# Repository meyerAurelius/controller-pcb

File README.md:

# controller-pcb
Controller PCB for the Digital Dash on the UCalgary BAJA Student design team

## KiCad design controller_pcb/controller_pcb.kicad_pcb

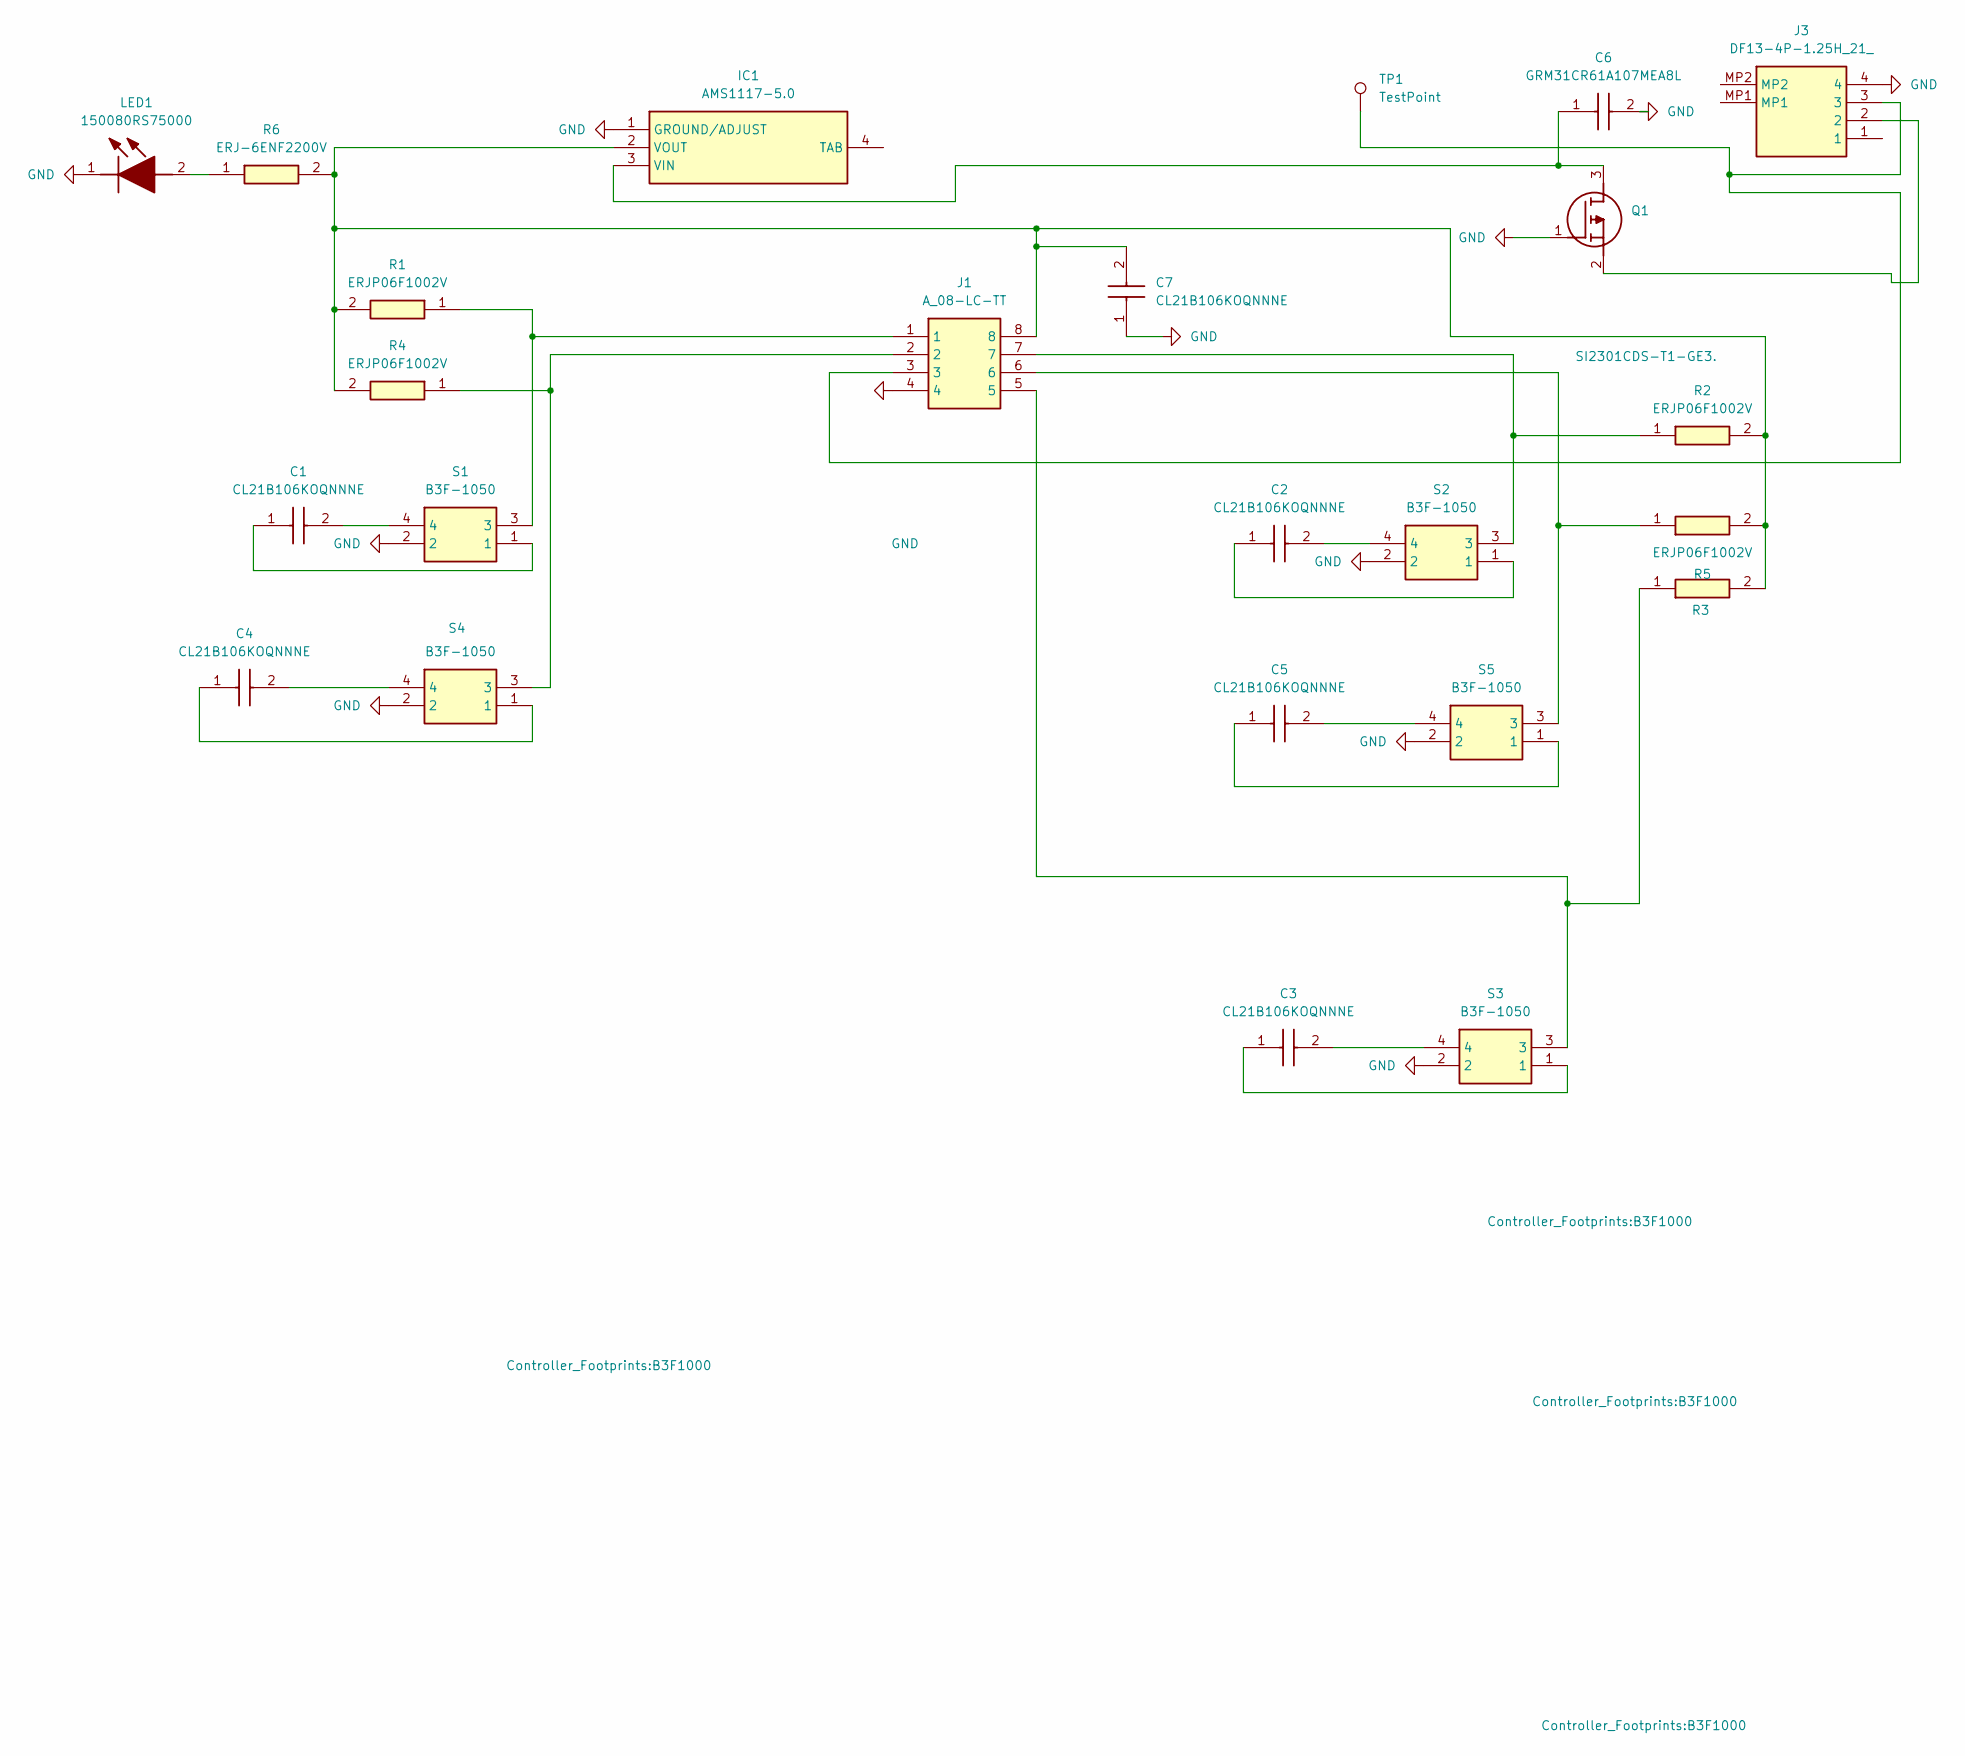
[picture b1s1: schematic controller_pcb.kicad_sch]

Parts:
C1, C2, C3, C4, C5, C7: CL21B106KOQNNNE; CAPC2012X140N; Manufacturer_Part_Number CL21B106KOQNNNE; Mouser Part Number 187-CL21B106KOQNNNE
C6: GRM31CR61A107MEA8L; GRM31x; Manufacturer_Part_Number GRM31CR61A107MEA8L; Mouser Part Number 81-GRM31CR61A107MA8L
IC1: AMS1117-5.0; SOT229P700X180-4N; Manufacturer_Part_Number AMS1117-5.0
J1: A_08-LC-TT; DIPS762W61P254L1016H525Q8N; Manufacturer_Part_Number A 08-LC-TT
J3: DF13-4P-1.25H_21_; DF134P125H21; Manufacturer_Part_Number DF13-4P-1.25H(21); Mouser Part Number 798-DF134P125H21
LED1: 150080RS75000; LEDC2012X70N; Manufacturer_Part_Number 150080RS75000; Mouser Part Number 710-150080RS75000
Q1: SI2301CDS-T1-GE3.; SOT95P237X112-3N; Manufacturer_Part_Number SI2301CDS-T1-GE3.
R1, R2, R3, R4, R5: ERJP06F1002V; ERJP06D1000V; Manufacturer_Part_Number ERJP06F1002V
R6: ERJ-6ENF2200V; ERJ6ENF1000V; Manufacturer_Part_Number ERJ-6ENF2200V; Mouser Part Number 667-ERJ-6ENF2200V
S1, S2, S3, S4, S5: B3F-1050; B3F1000; Manufacturer_Part_Number B3F-1050; Mouser Part Number 653-B3F-1050
TP1: TestPoint; TestPoint_Pad_2.0x2.0mm

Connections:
GND: C6.2, C7.1, IC1.1 (GROUND/ADJUST), J1.4, J3.4, LED1.1 (K), Q1.1 (G), S1.2, S2.2, S3.2, S4.2, S5.2
unnamed: C1.1, S1.1
unnamed: C1.2, S1.4
unnamed: C2.1, S2.1
unnamed: C2.2, S2.4
unnamed: C3.1, S3.1
unnamed: C3.2, S3.4
unnamed: C4.1, S4.1
unnamed: C4.2, S4.4
unnamed: C5.1, S5.1
unnamed: C5.2, S5.4
unnamed: C6.1, IC1.3 (VIN), Q1.3 (D)
unnamed: C7.2, IC1.2 (VOUT), J1.8, R1.2, R2.2, R3.2, R4.2, R5.2, R6.2
unnamed: J1.1, R1.1, S1.3
unnamed: J1.2, R4.1, S4.3
unnamed: J1.3, J3.3, TP1.1
unnamed: J1.5, R3.1, S3.3
unnamed: J1.6, R5.1, S5.3
unnamed: J1.7, R2.1, S2.3
unnamed: LED1.2 (A), R6.1
unnamed: J3.2, Q1.2 (S)

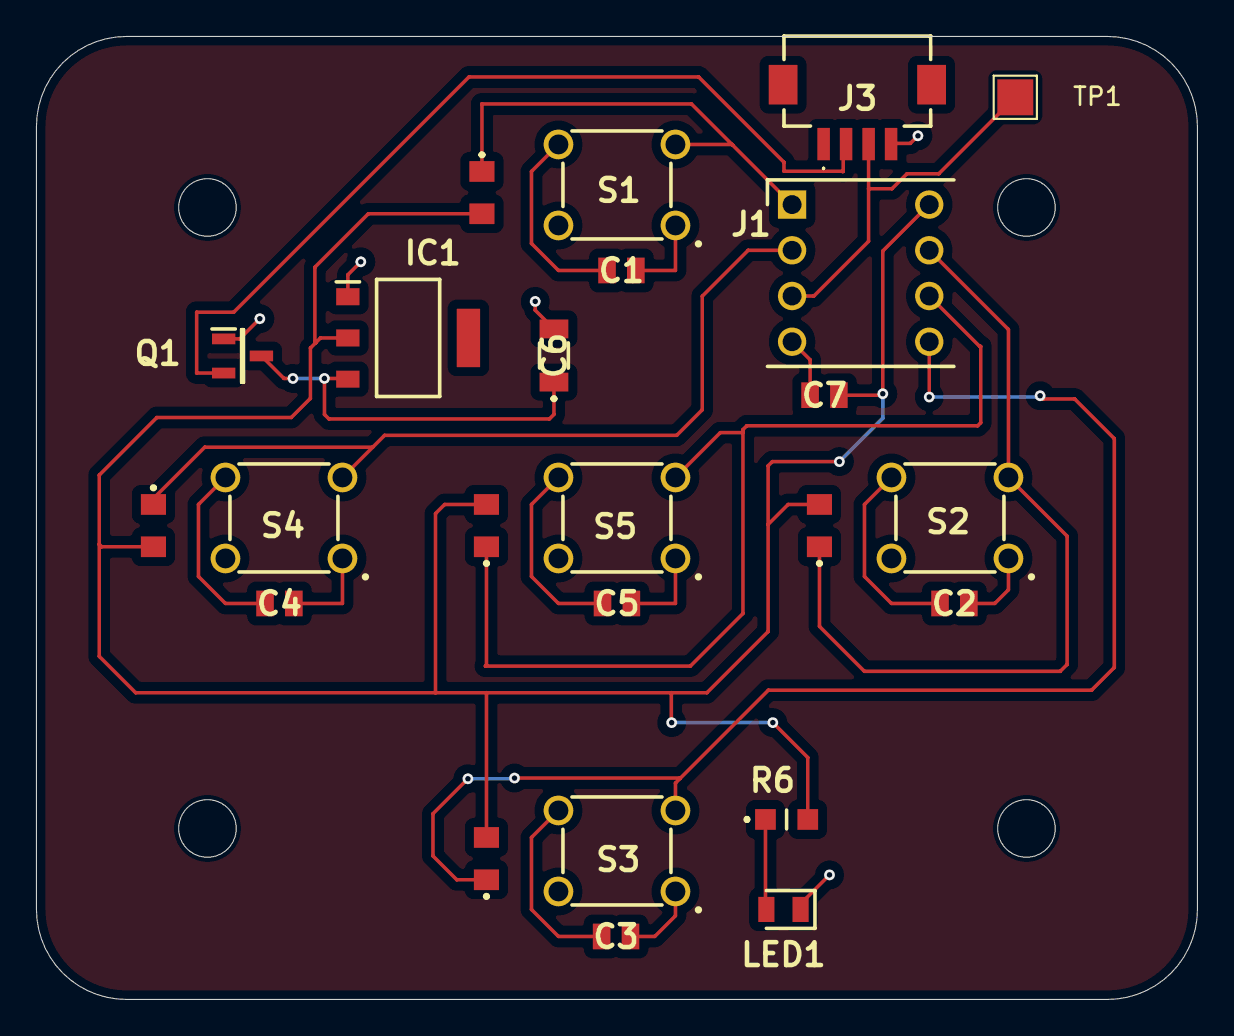
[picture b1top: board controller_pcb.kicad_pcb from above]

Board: 2 copper layers, 64.5 x 53.5 mm, 24 parts (0 on the bottom side), 21 nets.

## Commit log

2026-02-21 Created project
2026-02-21 Imported symbols and footprints
2026-02-21 Started placing and wiring
2026-02-26 Finished schematic, updating PCB
2026-02-26 Updated unsaved changes
2026-02-28 PCB layout editing
2026-02-28 Placed most components, added mounting holes
2026-03-01 Saved unsaved changes
2026-03-05 Voltage regular and bulk capacitor added
2026-03-06 Replaced voltage regulator, added 3D files
2026-03-07 MOSFET, regulator, PWR_LED, JST added; half routed; ground plane created
2026-03-07 3D models added
2026-03-07 Finished routing; added copper plane on front
2026-03-07 Rerouted for button clearance
2026-03-07 Silkscreen labels and Baja logo
2026-03-08 added decoupling caps, modified silkscreen and some corners on routing
2026-03-21 added hirose DF13 to check footprints
2026-03-21 updated wiring and copper fill
